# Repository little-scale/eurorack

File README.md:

# Eurorack

Eurorack projects

http://little-scale.com/

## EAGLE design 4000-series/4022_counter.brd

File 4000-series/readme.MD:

# 4000 Series Modules

Simple, cheap CMOS Logic-based Eurorack modules. 

* 4022 Eight Stage Counter
* 4024 Seven Stage Binary Counter Module 
* 4028 Binary Addressable Sequencer Module
* 4093 Quad LFO

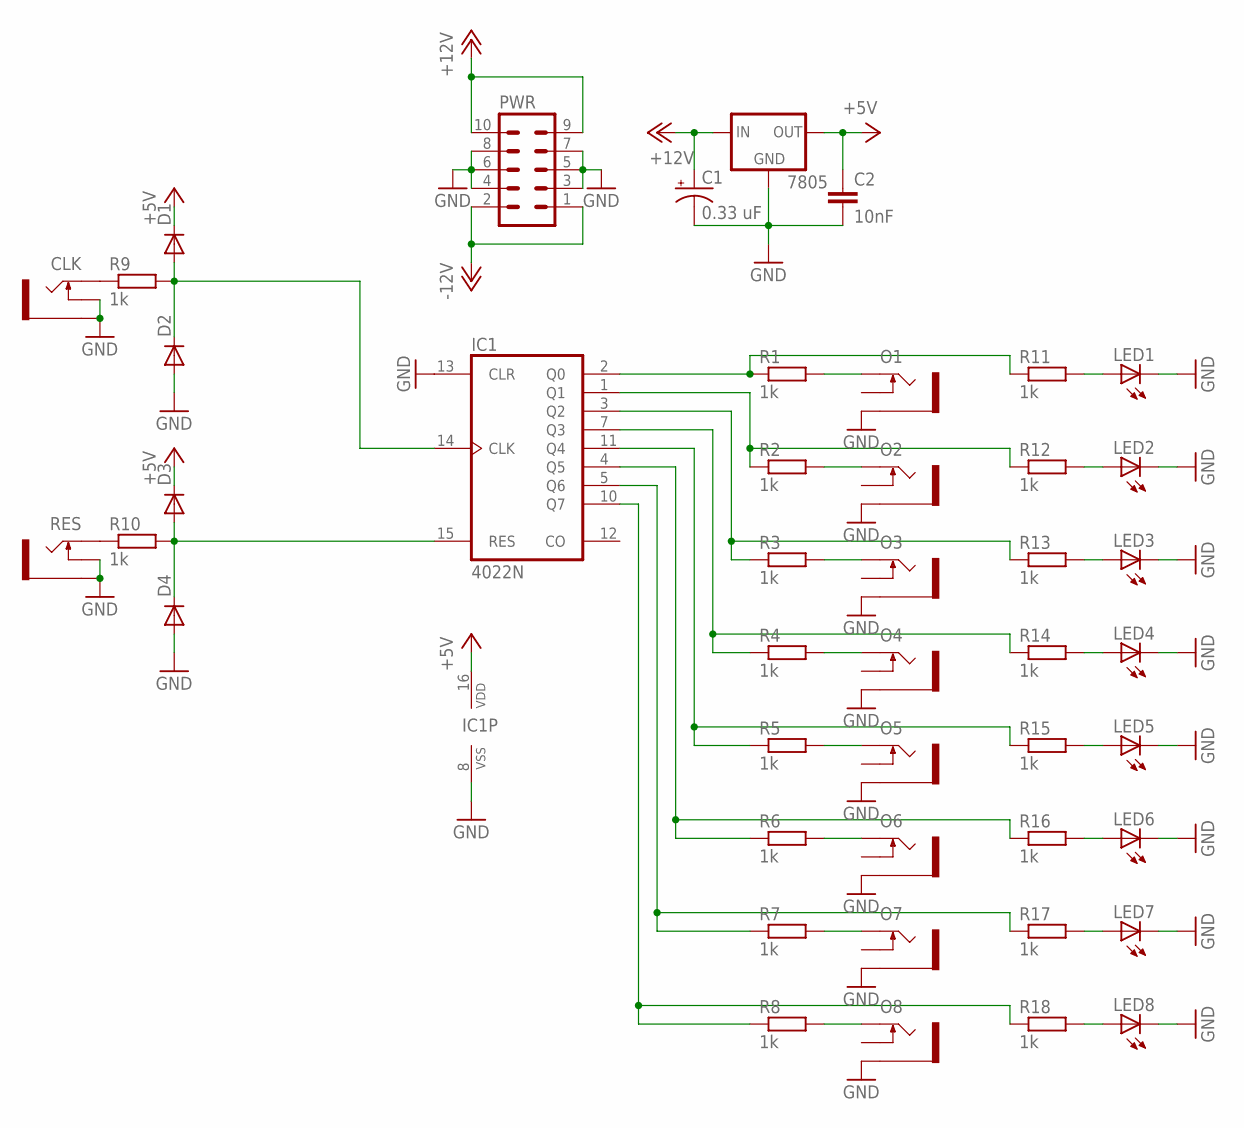
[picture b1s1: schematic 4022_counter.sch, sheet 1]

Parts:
7805: 78XXS
C1: 0.33 uF; E2,5-7
C2: 10nF; CAP-PTH-10MM
CLK: THONKICONNNEW; WQP-PJ301M-12_JACK
D1, D2, D3, D4: SMALL_DIODEDO35-7; DO35-7
IC1: 4022N; DIL16
LED1, LED2, LED3, LED4, LED5, LED6, LED7, LED8: LED3MM
O1, O2, O3, O4, O5, O6, O7, O8: THONKICONNNEW; WQP-PJ301M-12_JACK
PWR: EURO_POWER_HEADERFAT_PADS; EURO_PWR_HEADER_FAT
R1, R2, R3, R4, R5, R6, R7, R8, R9, R10, R11, R12, R13, R14, R15, R16, R17, R18: 1k; 7MM_RESISTOR
RES: THONKICONNNEW; WQP-PJ301M-12_JACK

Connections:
+5V: 7805.OUT, C2.1, D1.C, D3.C, IC1.16 (VDD)
+12V: 7805.IN, C1.+, PWR.9, PWR.10
-12V: PWR.1, PWR.2
GND: 7805.GND, C1.-, C2.2, CLK.P$2_SWITCH (SWITCH), CLK.P$3_SLEEVE (SLEEVE), D2.A, D4.A, IC1.8 (VSS), IC1.13 (CLR), LED1.K (C), LED2.K (C), LED3.K (C), LED4.K (C), LED5.K (C), LED6.K (C), LED7.K (C), LED8.K (C), O1.P$3_SLEEVE (SLEEVE), O2.P$3_SLEEVE (SLEEVE), O3.P$3_SLEEVE (SLEEVE), O4.P$3_SLEEVE (SLEEVE), O5.P$3_SLEEVE (SLEEVE), O6.P$3_SLEEVE (SLEEVE), O7.P$3_SLEEVE (SLEEVE), O8.P$3_SLEEVE (SLEEVE), PWR.3, PWR.4, PWR.5, PWR.6, PWR.7, PWR.8, RES.P$2_SWITCH (SWITCH), RES.P$3_SLEEVE (SLEEVE)
unnamed: CLK.P$1_TIP (TIP), R9.1
unnamed: R10.1, RES.P$1_TIP (TIP)
unnamed: IC1.1 (Q1), R2.1, R12.1
unnamed: IC1.3 (Q2), R3.1, R13.1
unnamed: IC1.7 (Q3), R4.1, R14.1
unnamed: IC1.11 (Q4), R5.1, R15.1
unnamed: O1.P$1_TIP (TIP), R1.2
unnamed: O2.P$1_TIP (TIP), R2.2
unnamed: O3.P$1_TIP (TIP), R3.2
unnamed: D1.A, D2.C, IC1.14 (CLK), R9.2
unnamed: IC1.2 (Q0), R1.1, R11.1
unnamed: D3.A, D4.C, IC1.15 (RES), R10.2
unnamed: LED1.A, R11.2
unnamed: O4.P$1_TIP (TIP), R4.2
unnamed: LED2.A, R12.2
unnamed: O5.P$1_TIP (TIP), R5.2
unnamed: LED3.A, R13.2
unnamed: O6.P$1_TIP (TIP), R6.2
unnamed: LED4.A, R14.2
unnamed: O7.P$1_TIP (TIP), R7.2
unnamed: LED5.A, R15.2
unnamed: IC1.4 (Q5), R6.1, R16.1
unnamed: LED6.A, R16.2
unnamed: IC1.5 (Q6), R7.1, R17.1
unnamed: LED7.A, R17.2
unnamed: IC1.10 (Q7), R8.1, R18.1
unnamed: LED8.A, R18.2
unnamed: O8.P$1_TIP (TIP), R8.2

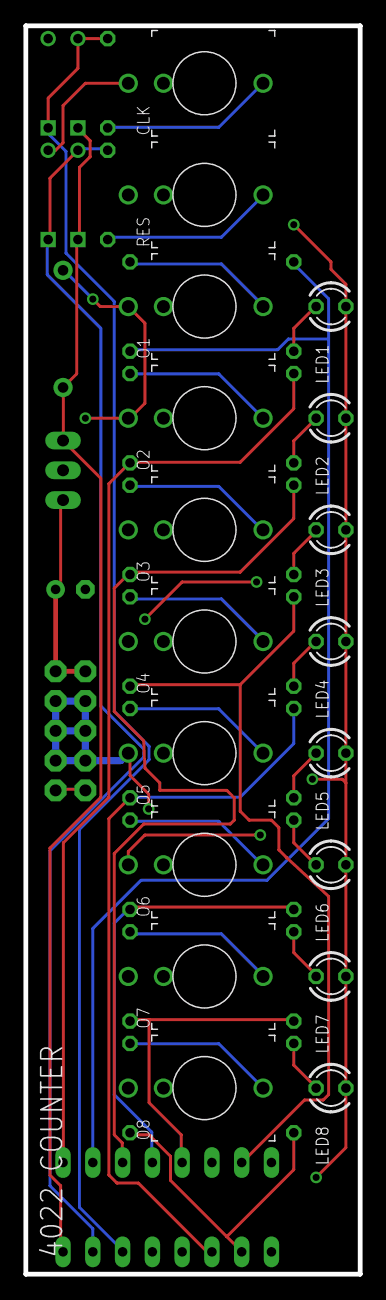
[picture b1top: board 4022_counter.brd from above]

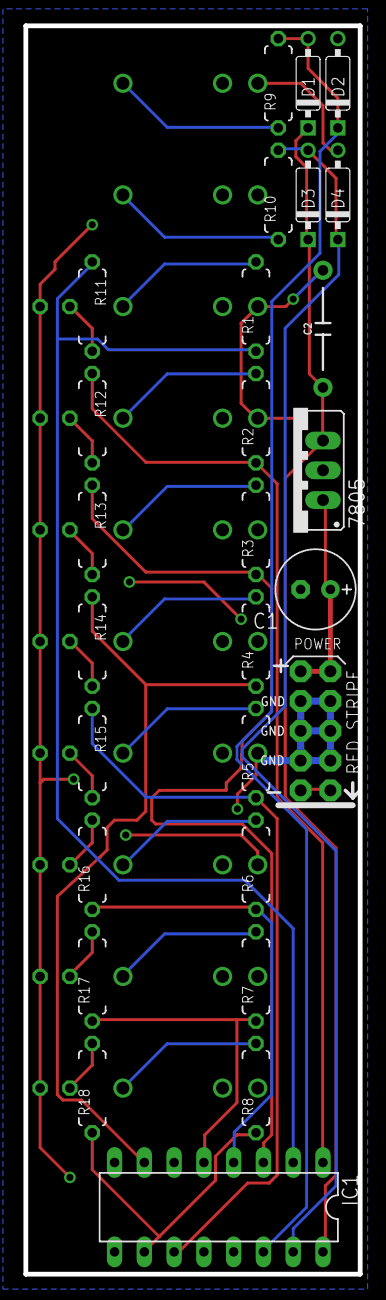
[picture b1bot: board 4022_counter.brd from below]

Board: 2 copper layers, 28.5 x 106.5 mm, 45 parts (27 on the bottom side), 32 nets.

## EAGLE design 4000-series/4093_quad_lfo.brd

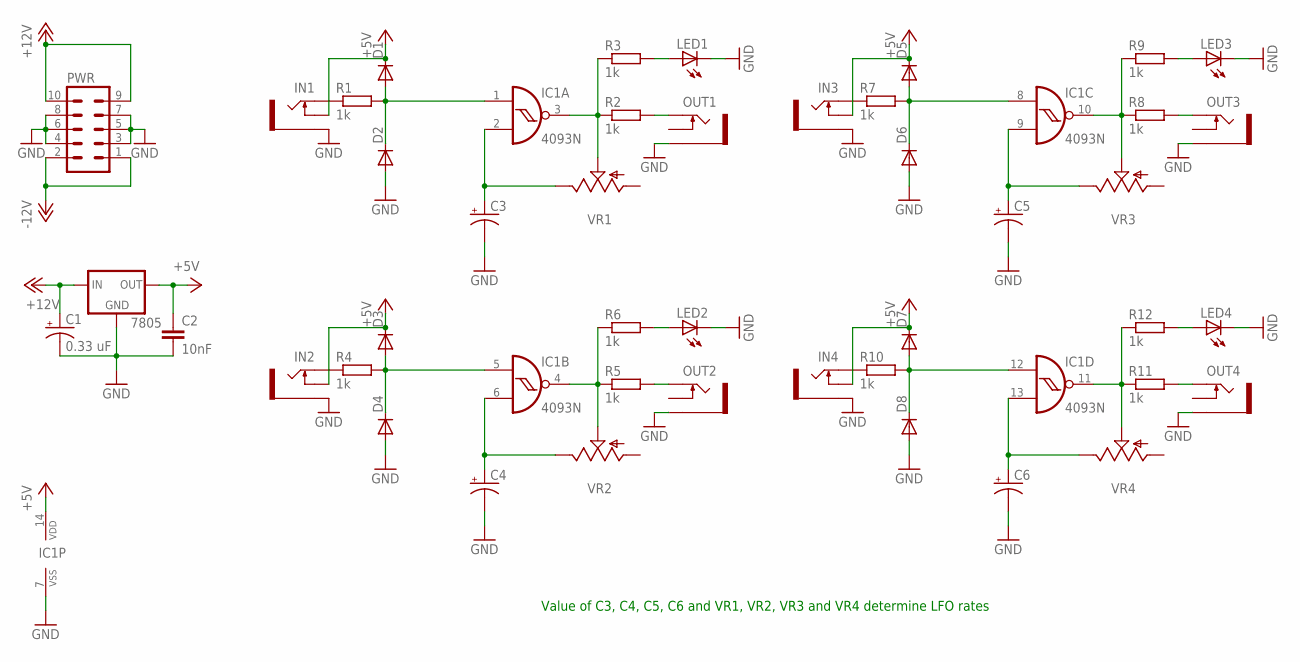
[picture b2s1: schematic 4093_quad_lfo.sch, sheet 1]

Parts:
7805: 78XXS
C1: 0.33 uF; E2,5-7
C2: 10nF; CAP-PTH-10MM
C3, C4, C5, C6: CPOL-USE2.5-7; E2,5-7
D1, D2, D3, D4, D5, D6, D7, D8: SMALL_DIODEDO35-7; DO35-7
IC1: 4093N; DIL14
IN1, IN2, IN3, IN4: THONKICONNNEW; WQP-PJ301M-12_JACK
LED1, LED2, LED3, LED4: LED3MM
OUT1, OUT2, OUT3, OUT4: THONKICONNNEW; WQP-PJ301M-12_JACK
PWR: EURO_POWER_HEADERFAT_PADS; EURO_PWR_HEADER_FAT
R1, R2, R3, R4, R5, R6, R7, R8, R9, R10, R11, R12: 1k; 7MM_RESISTOR
VR1, VR2, VR3, VR4: 9MM_SNAP-IN_POT_; 9MM_SNAP-IN_POT

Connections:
+5V: 7805.OUT, C2.1, D1.C, D3.C, D5.C, D7.C, IC1.14 (VDD), IN1.P$2_SWITCH (SWITCH), IN2.P$2_SWITCH (SWITCH), IN3.P$2_SWITCH (SWITCH), IN4.P$2_SWITCH (SWITCH)
+12V: 7805.IN, C1.+, PWR.9, PWR.10
-12V: PWR.1, PWR.2
GND: 7805.GND, C1.-, C2.2, C3.-, C4.-, C5.-, C6.-, D2.A, D4.A, D6.A, D8.A, IC1.7 (VSS), IN1.P$3_SLEEVE (SLEEVE), IN2.P$3_SLEEVE (SLEEVE), IN3.P$3_SLEEVE (SLEEVE), IN4.P$3_SLEEVE (SLEEVE), LED1.K (C), LED2.K (C), LED3.K (C), LED4.K (C), OUT1.P$3_SLEEVE (SLEEVE), OUT2.P$3_SLEEVE (SLEEVE), OUT3.P$3_SLEEVE (SLEEVE), OUT4.P$3_SLEEVE (SLEEVE), PWR.3, PWR.4, PWR.5, PWR.6, PWR.7, PWR.8
unnamed: IN1.P$1_TIP (TIP), R1.1
unnamed: D3.A, D4.C, IC1.5 (I0), R4.2
unnamed: LED1.A, R3.2
unnamed: C3.+, IC1.2 (I1), VR1.3 (E)
unnamed: IC1.3 (O), R2.1, R3.1, VR1.2 (S)
unnamed: OUT1.P$1_TIP (TIP), R2.2
unnamed: IN2.P$1_TIP (TIP), R4.1
unnamed: C4.+, IC1.6 (I1), VR2.3 (E)
unnamed: IC1.4 (O), R5.1, R6.1, VR2.2 (S)
unnamed: OUT2.P$1_TIP (TIP), R5.2
unnamed: LED2.A, R6.2
unnamed: D5.A, D6.C, IC1.8 (I0), R7.2
unnamed: IN3.P$1_TIP (TIP), R7.1
unnamed: C5.+, IC1.9 (I1), VR3.3 (E)
unnamed: IC1.10 (O), R8.1, R9.1, VR3.2 (S)
unnamed: OUT3.P$1_TIP (TIP), R8.2
unnamed: LED3.A, R9.2
unnamed: D1.A, D2.C, IC1.1 (I0), R1.2
unnamed: D7.A, D8.C, IC1.12 (I0), R10.2
unnamed: IN4.P$1_TIP (TIP), R10.1
unnamed: C6.+, IC1.13 (I1), VR4.3 (E)
unnamed: IC1.11 (O), R11.1, R12.1, VR4.2 (S)
unnamed: OUT4.P$1_TIP (TIP), R11.2
unnamed: LED4.A, R12.2

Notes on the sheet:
Value of C3, C4, C5, C6 and VR1, VR2, VR3 and VR4 determine LFO rates

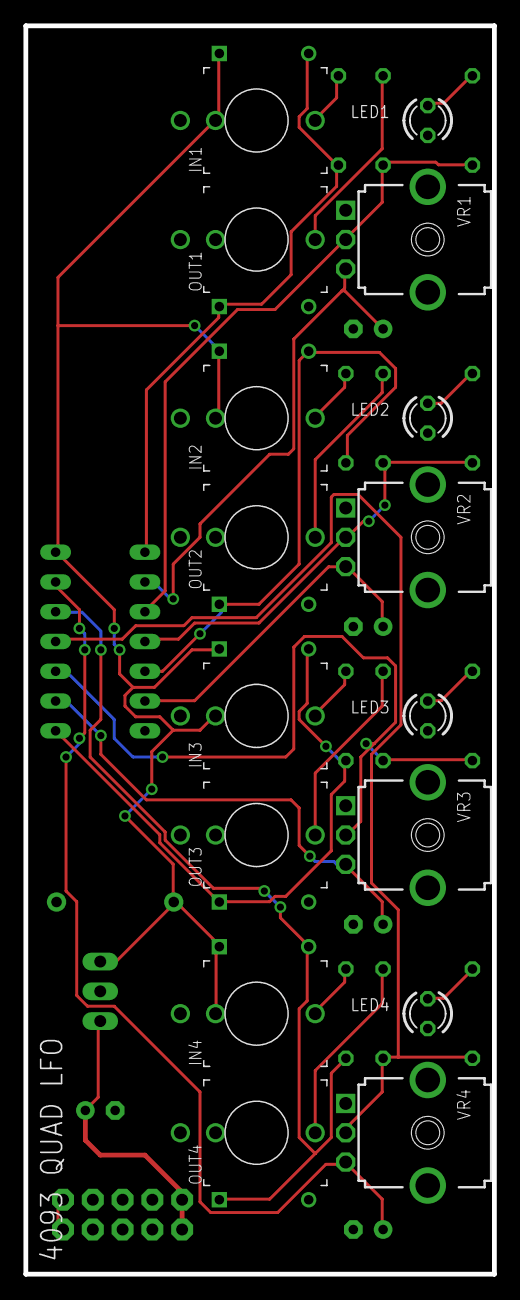
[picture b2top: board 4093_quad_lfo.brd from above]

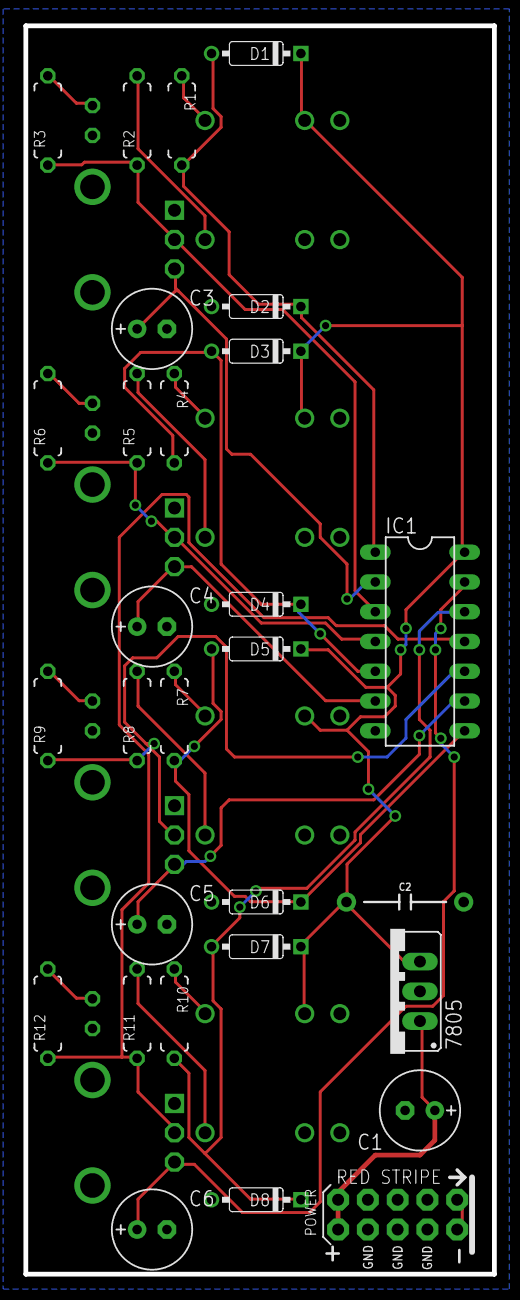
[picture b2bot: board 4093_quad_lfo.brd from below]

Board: 2 copper layers, 40.0 x 106.5 mm, 45 parts (29 on the bottom side), 28 nets.

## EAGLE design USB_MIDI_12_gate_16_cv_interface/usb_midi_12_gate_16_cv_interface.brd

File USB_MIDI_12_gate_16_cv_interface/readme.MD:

This is a USB-powered, Teensy-based interface that has 16 CV outputs and 12 gate outputs. 
USB MIDI channels 1 - 8 are mapped to CV outputs 1 - 16 for pitch and velocity, and gates 1 - 8 for note on and off events. 
Gates 9 - 12 are mapped to note on and off events only on channel 9, 
and also will send a sync and transport signal based on MIDI clock messages if received. 
CV is 12 bit from 0V to 4V, gates 1 - 8 are 0 and 5V, and gates 9 - 12 are 0 and 3.3v.

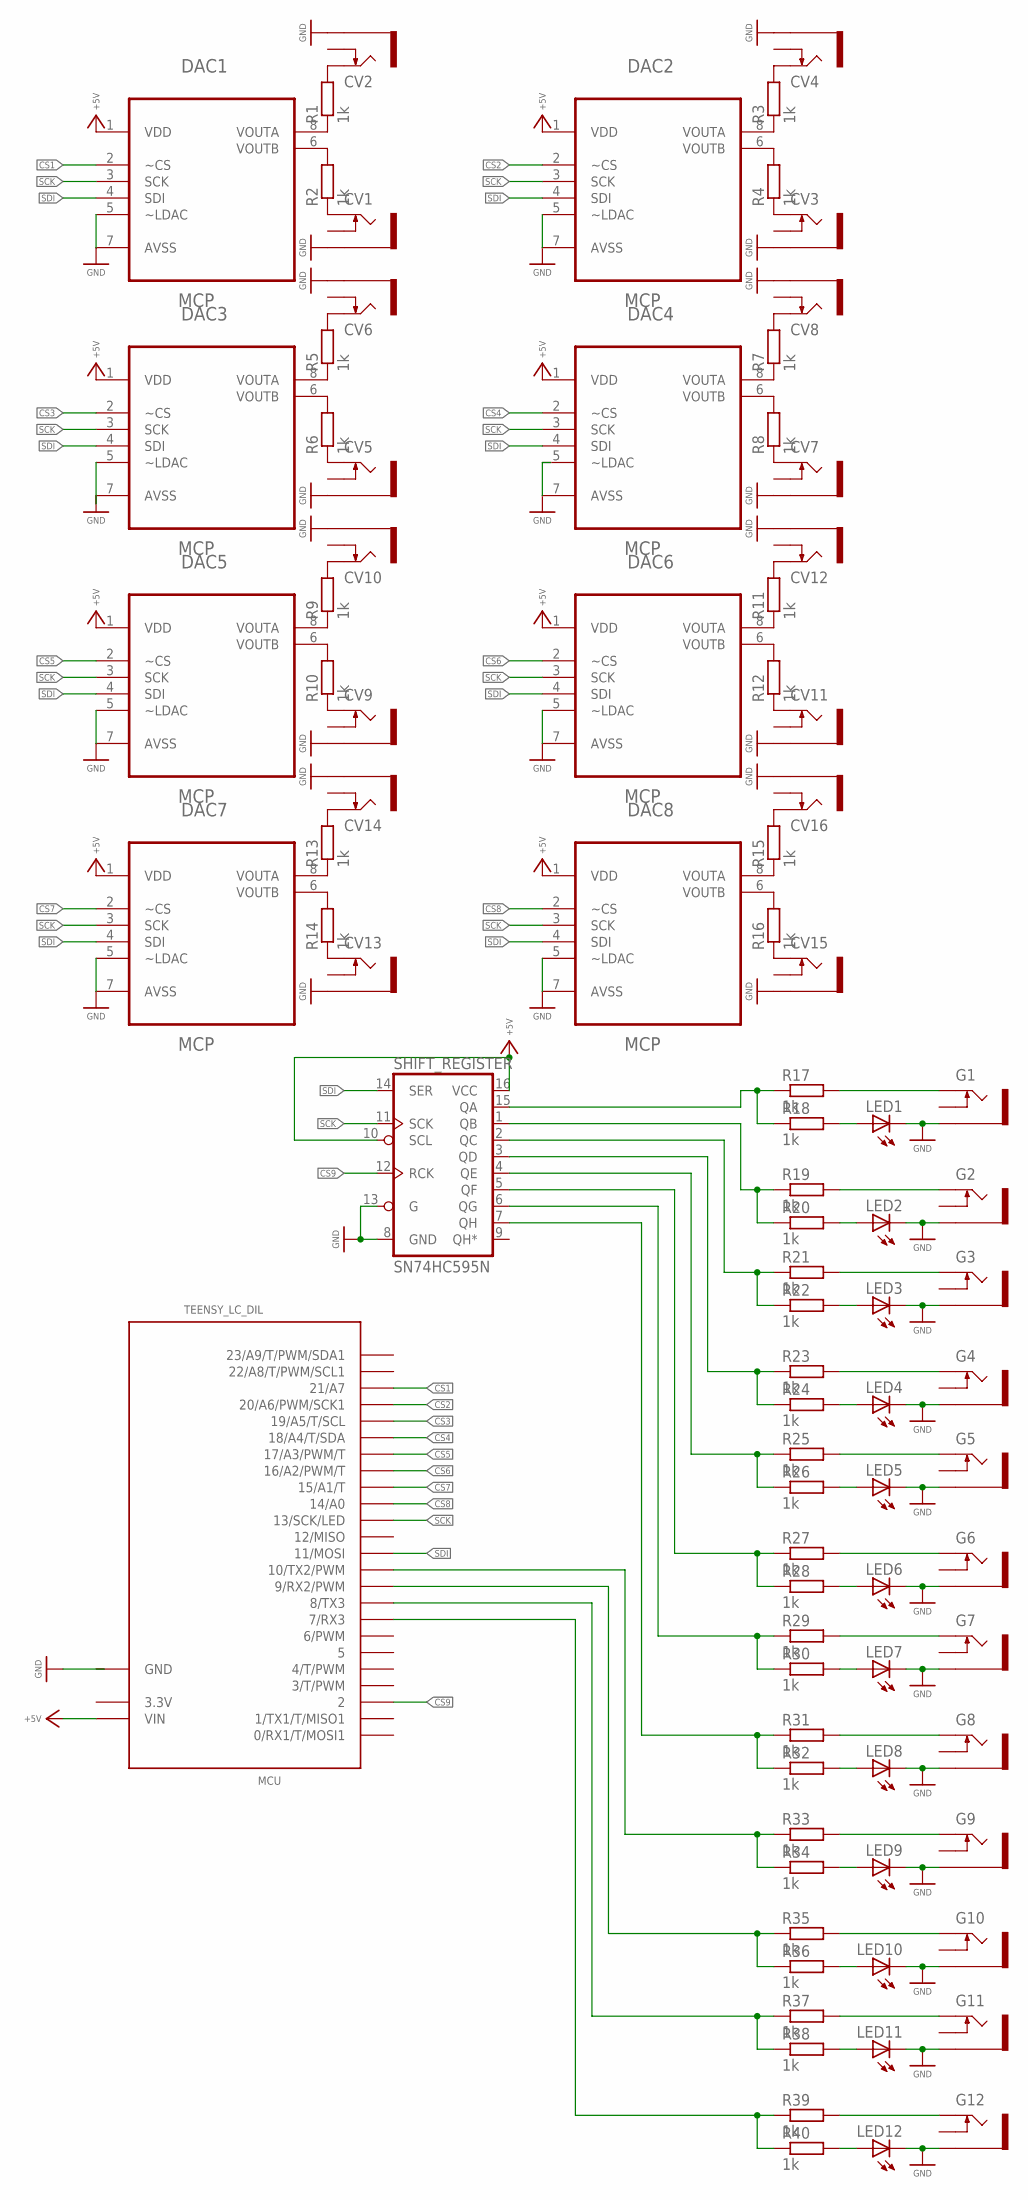
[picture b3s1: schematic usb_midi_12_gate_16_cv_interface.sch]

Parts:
CV1, CV2, CV3, CV4, CV5, CV6, CV7, CV8, CV9, CV10, CV11, CV12, CV13, CV14, CV15, CV16: THONKICONNNEW; WQP-PJ301M-12_JACK
DAC1, DAC2, DAC3, DAC4, DAC5, DAC6, DAC7, DAC8: MCP; DIP254P762X432-8
G1, G2, G3, G4, G5, G6, G7, G8, G9, G10, G11, G12: THONKICONNNEW; WQP-PJ301M-12_JACK
LED1, LED2, LED3, LED4, LED5, LED6, LED7, LED8, LED9, LED10, LED11, LED12: LED3MM
MCU: TEENSY_LC_DIL; TEENSY_3.0-3.2&LC_DIL
R1, R2, R3, R4, R5, R6, R7, R8, R9, R10, R11, R12, R13, R14, R15, R16, R17, R18, R19, R20, R21, R22, R23, R24, R25, R26, R27, R28, R29, R30, R31, R32, R33, R34, R35, R36, R37, R38, R39, R40: 1k; 10MM_RESISTOR
SHIFT_REGISTER: SN74HC595N; DIP16

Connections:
3.3V: MCU.3.3V
+5V: DAC1.1 (VDD), DAC2.1 (VDD), DAC3.1 (VDD), DAC4.1 (VDD), DAC5.1 (VDD), DAC6.1 (VDD), DAC7.1 (VDD), DAC8.1 (VDD), MCU.VIN, SHIFT_REGISTER.10 (SCL), SHIFT_REGISTER.16 (VCC)
CS1: DAC1.2 (~CS), MCU.21/A7
CS2: DAC2.2 (~CS), MCU.20/A6 (20/A6/PWM/SCK1)
CS3: DAC3.2 (~CS), MCU.19/A5 (19/A5/T/SCL)
CS4: DAC4.2 (~CS), MCU.18/A4 (18/A4/T/SDA)
CS5: DAC5.2 (~CS), MCU.17/A3 (17/A3/PWM/T)
CS6: DAC6.2 (~CS), MCU.16/A2 (16/A2/PWM/T)
CS7: DAC7.2 (~CS), MCU.15/A1 (15/A1/T)
CS8: DAC8.2 (~CS), MCU.14/A0
CS9: MCU.2, SHIFT_REGISTER.12 (RCK)
GND: CV1.P$3_SLEEVE (SLEEVE), CV2.P$3_SLEEVE (SLEEVE), CV3.P$3_SLEEVE (SLEEVE), CV4.P$3_SLEEVE (SLEEVE), CV5.P$3_SLEEVE (SLEEVE), CV6.P$3_SLEEVE (SLEEVE), CV7.P$3_SLEEVE (SLEEVE), CV8.P$3_SLEEVE (SLEEVE), CV9.P$3_SLEEVE (SLEEVE), CV10.P$3_SLEEVE (SLEEVE), CV11.P$3_SLEEVE (SLEEVE), CV12.P$3_SLEEVE (SLEEVE), CV13.P$3_SLEEVE (SLEEVE), CV14.P$3_SLEEVE (SLEEVE), CV15.P$3_SLEEVE (SLEEVE), CV16.P$3_SLEEVE (SLEEVE), DAC1.5 (~LDAC), DAC1.7 (AVSS), DAC2.5 (~LDAC), DAC2.7 (AVSS), DAC3.7 (AVSS), DAC4.7 (AVSS), DAC5.5 (~LDAC), DAC5.7 (AVSS), DAC6.5 (~LDAC), DAC6.7 (AVSS), DAC7.5 (~LDAC), DAC7.7 (AVSS), DAC8.5 (~LDAC), DAC8.7 (AVSS), G1.P$3_SLEEVE (SLEEVE), G2.P$3_SLEEVE (SLEEVE), G3.P$3_SLEEVE (SLEEVE), G4.P$3_SLEEVE (SLEEVE), G5.P$3_SLEEVE (SLEEVE), G6.P$3_SLEEVE (SLEEVE), G7.P$3_SLEEVE (SLEEVE), G8.P$3_SLEEVE (SLEEVE), G9.P$3_SLEEVE (SLEEVE), G10.P$3_SLEEVE (SLEEVE), G11.P$3_SLEEVE (SLEEVE), G12.P$3_SLEEVE (SLEEVE), LED1.K (C), LED2.K (C), LED3.K (C), LED4.K (C), LED5.K (C), LED6.K (C), LED7.K (C), LED8.K (C), LED9.K (C), LED10.K (C), LED11.K (C), LED12.K (C), MCU.AGND (GND), MCU.GND, SHIFT_REGISTER.8 (GND), SHIFT_REGISTER.13 (G)
unnamed: DAC1.6 (VOUTB), R2.2
unnamed: DAC1.8 (VOUTA), R1.1
unnamed: DAC2.8 (VOUTA), R3.1
unnamed: DAC2.6 (VOUTB), R4.2
unnamed: DAC3.8 (VOUTA), R5.1
unnamed: DAC3.6 (VOUTB), R6.2
unnamed: DAC4.8 (VOUTA), R7.1
unnamed: DAC4.6 (VOUTB), R8.2
unnamed: DAC5.8 (VOUTA), R9.1
unnamed: DAC5.6 (VOUTB), R10.2
unnamed: DAC6.8 (VOUTA), R11.1
unnamed: DAC6.6 (VOUTB), R12.2
unnamed: DAC7.8 (VOUTA), R13.1
unnamed: DAC7.6 (VOUTB), R14.2
unnamed: DAC8.8 (VOUTA), R15.1
unnamed: DAC8.6 (VOUTB), R16.2
unnamed: CV1.P$1_TIP (TIP), R2.1
unnamed: CV2.P$1_TIP (TIP), R1.2
unnamed: CV4.P$1_TIP (TIP), R3.2
unnamed: CV3.P$1_TIP (TIP), R4.1
unnamed: CV5.P$1_TIP (TIP), R6.1
unnamed: CV6.P$1_TIP (TIP), R5.2
unnamed: CV7.P$1_TIP (TIP), R8.1
unnamed: CV8.P$1_TIP (TIP), R7.2
unnamed: CV9.P$1_TIP (TIP), R10.1
unnamed: CV10.P$1_TIP (TIP), R9.2
unnamed: CV11.P$1_TIP (TIP), R12.1
unnamed: CV12.P$1_TIP (TIP), R11.2
unnamed: CV13.P$1_TIP (TIP), R14.1
unnamed: CV14.P$1_TIP (TIP), R13.2
unnamed: CV15.P$1_TIP (TIP), R16.1
unnamed: CV16.P$1_TIP (TIP), R15.2
unnamed: G9.P$1_TIP (TIP), R33.2
unnamed: LED9.A, R34.2
unnamed: MCU.10 (10/TX2/PWM), R33.1, R34.1
unnamed: G10.P$1_TIP (TIP), R35.2
unnamed: LED10.A, R36.2
unnamed: MCU.9 (9/RX2/PWM), R35.1, R36.1
unnamed: G11.P$1_TIP (TIP), R37.2
unnamed: LED11.A, R38.2
unnamed: MCU.8 (8/TX3), R37.1, R38.1
unnamed: G12.P$1_TIP (TIP), R39.2
unnamed: LED12.A, R40.2
unnamed: MCU.7 (7/RX3), R39.1, R40.1
unnamed: G1.P$1_TIP (TIP), R17.2
unnamed: R17.1, R18.1, SHIFT_REGISTER.15 (QA)
unnamed: LED1.A, R18.2
unnamed: G2.P$1_TIP (TIP), R19.2
unnamed: LED2.A, R20.2
unnamed: R19.1, R20.1, SHIFT_REGISTER.1 (QB)
unnamed: G3.P$1_TIP (TIP), R21.2
unnamed: LED3.A, R22.2
unnamed: R21.1, R22.1, SHIFT_REGISTER.2 (QC)
unnamed: G4.P$1_TIP (TIP), R23.2
unnamed: LED4.A, R24.2
unnamed: R23.1, R24.1, SHIFT_REGISTER.3 (QD)
unnamed: G5.P$1_TIP (TIP), R25.2
unnamed: LED5.A, R26.2
unnamed: R25.1, R26.1, SHIFT_REGISTER.4 (QE)
unnamed: G6.P$1_TIP (TIP), R27.2
unnamed: LED6.A, R28.2
unnamed: R27.1, R28.1, SHIFT_REGISTER.5 (QF)
unnamed: G7.P$1_TIP (TIP), R29.2
unnamed: LED7.A, R30.2
unnamed: R29.1, R30.1, SHIFT_REGISTER.6 (QG)
unnamed: G8.P$1_TIP (TIP), R31.2
unnamed: LED8.A, R32.2
unnamed: R31.1, R32.1, SHIFT_REGISTER.7 (QH)
SCK: DAC1.3 (SCK), DAC2.3 (SCK), DAC3.3 (SCK), DAC4.3 (SCK), DAC5.3 (SCK), DAC6.3 (SCK), DAC7.3 (SCK), DAC8.3 (SCK), MCU.13 (13/SCK/LED), SHIFT_REGISTER.11 (SCK)
SDI: DAC1.4 (SDI), DAC2.4 (SDI), DAC3.4 (SDI), DAC4.4 (SDI), DAC5.4 (SDI), DAC6.4 (SDI), DAC7.4 (SDI), DAC8.4 (SDI), MCU.11 (11/MOSI), SHIFT_REGISTER.14 (SER)

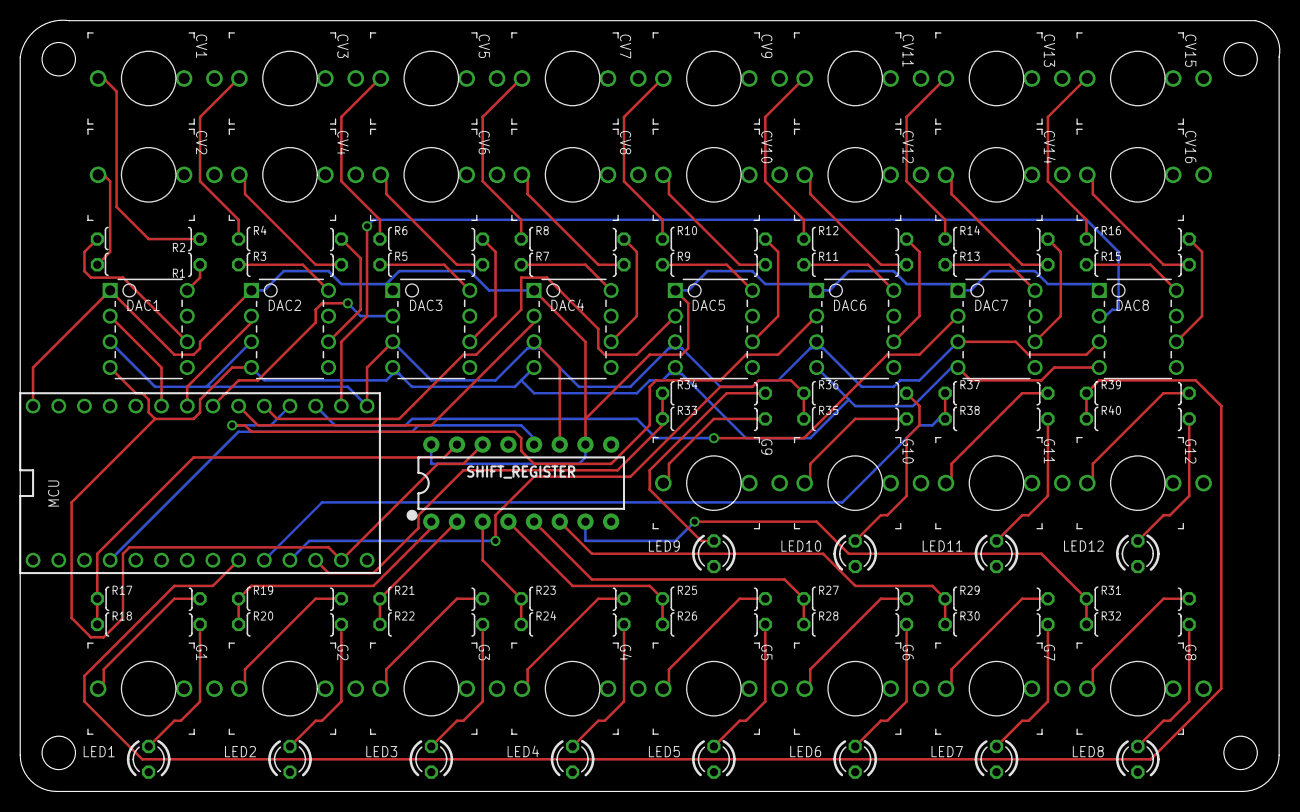
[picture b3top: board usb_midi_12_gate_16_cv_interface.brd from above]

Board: 2 copper layers, 124.5 x 76.2 mm, 90 parts (0 on the bottom side), 81 nets.

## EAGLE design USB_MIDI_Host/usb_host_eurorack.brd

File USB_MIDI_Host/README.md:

Examples of using Teensy 3.6 as a mediator between USB MIDI and Eurorack

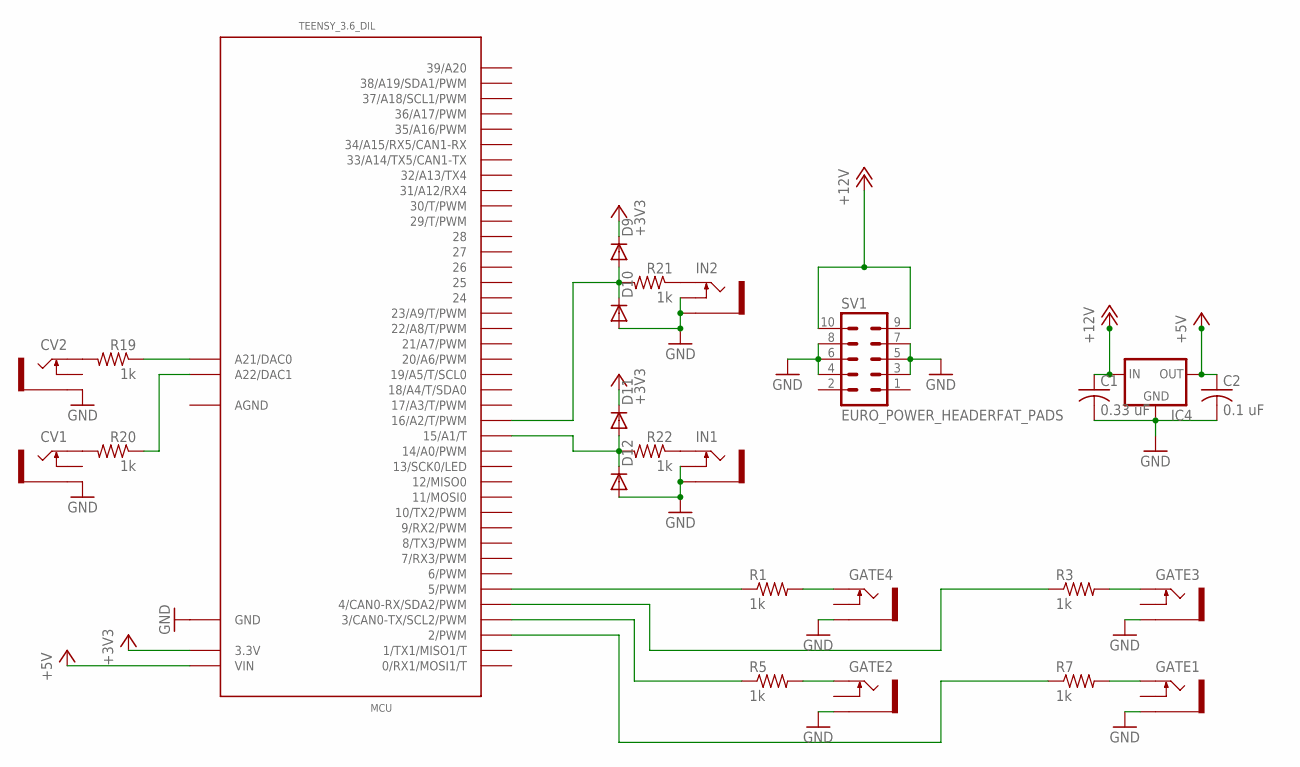
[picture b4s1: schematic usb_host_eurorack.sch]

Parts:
C1: 0.33 uF; C025-030X050
C2: 0.1 uF; C025-030X050
CV1, CV2: PJ302M
D9, D10, D11, D12: SMALL_DIODEDO35-7; DO35-7
GATE1, GATE2, GATE3, GATE4: PJ302M
IC4: 78XXL
IN1, IN2: PJ302M
MCU: TEENSY_3.6_DIL
R1, R3, R5, R7, R19, R20, R21, R22: 1k; 0207/10
SV1: EURO_POWER_HEADERFAT_PADS; EURO_PWR_HEADER_FAT

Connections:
+3V3: D9.C, D11.C, MCU.3.3V, MCU.3.3V3 (3.3V)
+5V: C2.1, IC4.OUT, MCU.VIN
+12V: C1.1, IC4.IN, SV1.9, SV1.10
AGND: MCU.AGND
GND: C1.2, C2.2, CV1.GND (SLEEVE), CV2.GND (SLEEVE), D10.A, D12.A, GATE1.GND (SLEEVE), GATE2.GND (SLEEVE), GATE3.GND (SLEEVE), GATE4.GND (SLEEVE), IC4.GND, IN1.GND (SLEEVE), IN1.SW (SWITCH), IN2.GND (SLEEVE), IN2.SW (SWITCH), MCU.GND, MCU.GND1 (GND), SV1.3, SV1.4, SV1.5, SV1.6, SV1.7, SV1.8
I1: D9.A, D10.C, MCU.16/A2 (16/A2/T/PWM), R21.2
I2: D11.A, D12.C, MCU.15/A1 (15/A1/T), R22.2
unnamed: GATE4.TIP, R1.2
unnamed: MCU.A22 (A22/DAC1), R20.1
unnamed: MCU.5 (5/PWM), R1.1
unnamed: GATE3.TIP, R3.2
unnamed: MCU.A21 (A21/DAC0), R19.1
unnamed: MCU.4 (4/CAN0-RX/SDA2/PWM), R3.1
unnamed: GATE2.TIP, R5.2
unnamed: MCU.3 (3/CAN0-TX/SCL2/PWM), R5.1
unnamed: GATE1.TIP, R7.2
unnamed: MCU.2 (2/PWM), R7.1
unnamed: IN2.TIP, R21.1
unnamed: IN1.TIP, R22.1
unnamed: CV2.TIP, R19.2
unnamed: CV1.TIP, R20.2

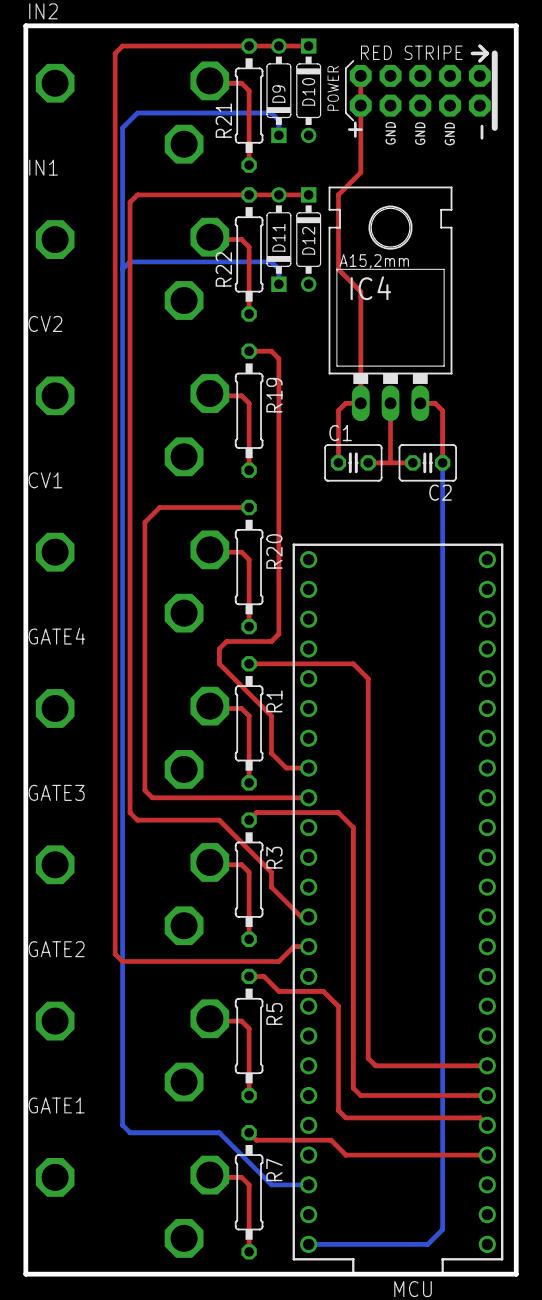
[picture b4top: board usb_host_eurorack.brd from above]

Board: 2 copper layers, 41.8 x 106.5 mm, 25 parts (0 on the bottom side), 20 nets.

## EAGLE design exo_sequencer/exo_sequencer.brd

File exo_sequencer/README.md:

# Exo Sequencer

A sixteen step sequencer with CV and trigger out. 

The step order is selected via a number of ways: 

• A gate signal sent to the INC input will increment the sequencer

• A gate signal sent to the DEC input will increment the sequencer

• An address as a four bit binary value (from 0000 to 1111) sent to A0, A1, A2 and A3 will select that step

• A voltage value sent to the STEP input will select that step

These methods of step selection are not mutually exclusive, and will operate simulatenously. 

The length control sets the length of the pattern. This can be modulated using a control voltage. 
The offset control sets the offset of the pattern. This can be modulated using a control voltage.

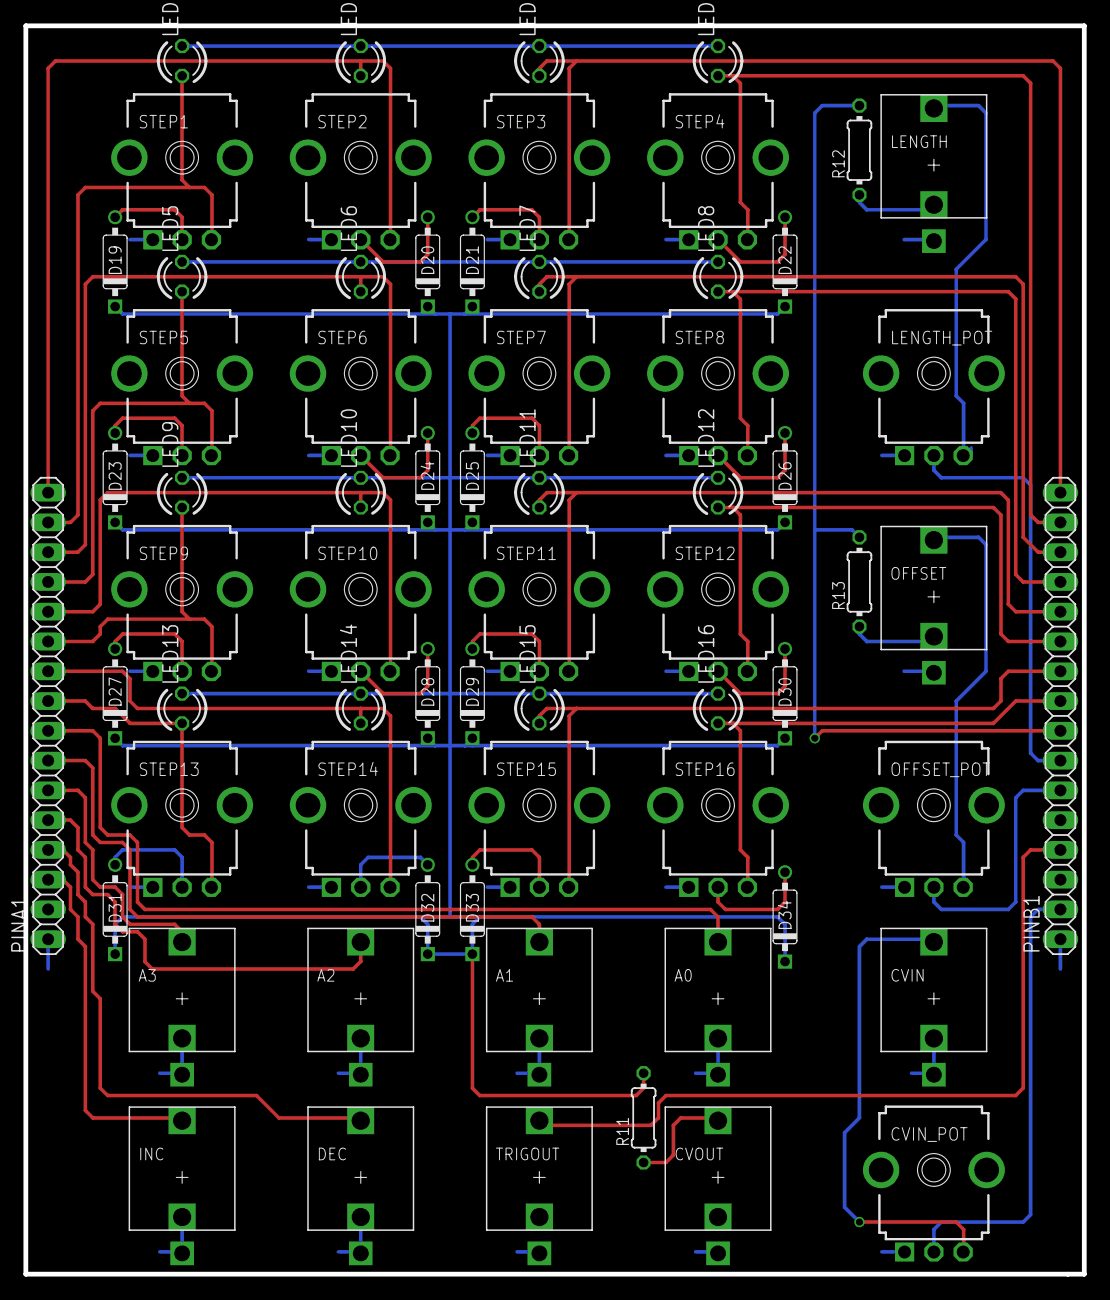
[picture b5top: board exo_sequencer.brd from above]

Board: 2 copper layers, 90.3 x 106.5 mm, 67 parts (0 on the bottom side), 18 nets.

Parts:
A0, A1, A2, A3: THONKICONN
CVIN: THONKICONN
CVIN_POT: 9MM_SNAP-IN_POT
CVOUT: THONKICONN
D19, D20, D21, D22, D23, D24, D25, D26, D27, D28, D29, D30, D31, D32, D33, D34: DO35-7
DEC: THONKICONN
INC: THONKICONN
LED1, LED2, LED3, LED4, LED5, LED6, LED7, LED8, LED9, LED10, LED11, LED12, LED13, LED14, LED15, LED16: LED3MM
LENGTH: THONKICONN
LENGTH_POT: 9MM_SNAP-IN_POT
OFFSET: THONKICONN
OFFSET_POT: 9MM_SNAP-IN_POT
PINA1: 1X16
PINB1: 1X16
R11, R12, R13: 0204/7
STEP1, STEP2, STEP3, STEP4, STEP5, STEP6, STEP7, STEP8, STEP9, STEP10, STEP11, STEP12, STEP13, STEP14, STEP15, STEP16: 9MM_SNAP-IN_POT
TRIGOUT: THONKICONN

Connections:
G: LED1.K, LED4.K, LED5.K, LED8.K, LED9.K, LED12.K, LED13.K, LED16.K, PINA1.1, PINB1.1
S$1: LED2.A, PINA1.16
S$2: LED1.A, PINA1.15
S$5: LED10.A, PINA1.12
S$6: LED16.A, PINB1.9
S$7: LED14.A, PINA1.10
S$8: LED13.A, PINA1.9
S$9: LED9.A, PINA1.11
S$10: LED3.A, PINB1.16
S$11: LED7.A, PINB1.14
S$12: LED4.A, PINB1.15
S$13: LED11.A, PINB1.12
S$14: LED8.A, PINB1.13
S$16: LED12.A, PINB1.11
S$35: D27.C, D28.C, D29.C, D30.C
S$38: D23.C, D24.C, D25.C, D26.C
S$49: PINB1.8, R12.2, R13.2
S$92: D19.C, D20.C, D21.C, D22.C, D31.C, D32.C, D33.C, D34.C, R11.2

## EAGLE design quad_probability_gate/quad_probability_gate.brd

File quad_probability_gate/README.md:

# Quad Probability Gate

A module that has one gate input, one cv input and four gate outputs. 

The cv input sets the likelihood (from 0% / 0v to 100% / 5v) that the input gate is mirrored at each of the four output gates. 

The probability for each output gate is calculated individually. 

Example video: https://www.youtube.com/watch?v=VjSLu_15tZ4

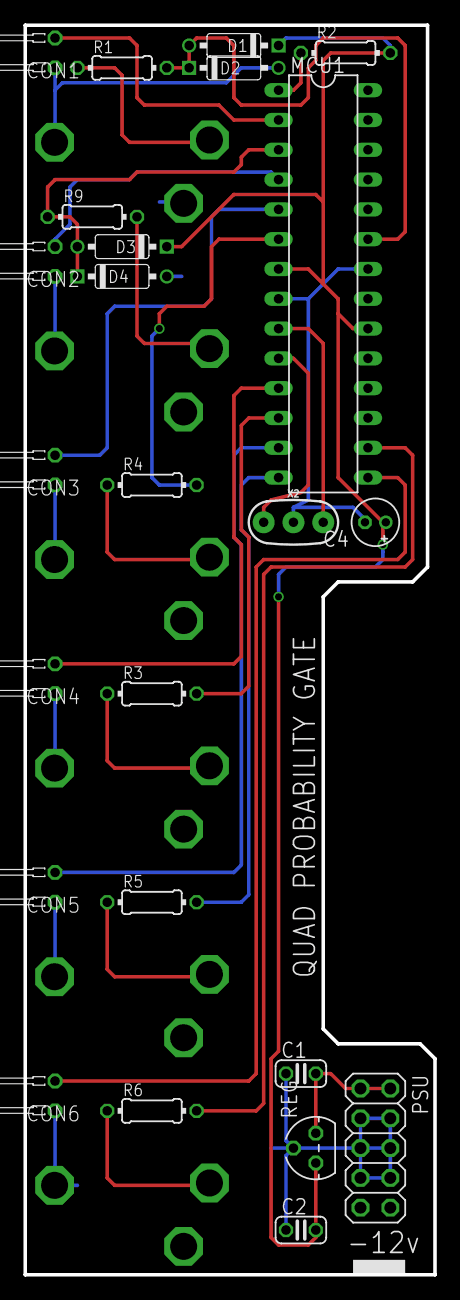
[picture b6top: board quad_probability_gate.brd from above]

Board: 2 copper layers, 34.9 x 106.5 mm, 30 parts (0 on the bottom side), 17 nets.

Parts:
C1, C2: C025-024X044
C4: E1,8-4
CON1, CON2, CON3, CON4, CON5, CON6: PJ302M
D1, D2, D3, D4: DO35-7
LED1, LED2, LED3, LED4, LED5, LED6: LED3MM_H7,5MM
MCU1: DIL28-3
PSU: 2X05
R1, R2, R3, R4, R5, R6, R9: 0204/7
REG: TO92
X2: RESONATOR-PTH-7.6X3.8

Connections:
G: C2.1, D4.A, LED1.A, LED2.A, LED3.A, LED4.A, LED5.A, LED6.A, MCU1.8, MCU1.22, PSU.3, PSU.4, PSU.5, PSU.6, PSU.7, PSU.8, REG.2, X2.2
S$2: LED1.K, MCU1.2
S$3: MCU1.10, X2.1
S$6: D4.C, MCU1.3, R9.1
S$7: MCU1.1, R2.1
S$8: C1.2, PSU.2, REG.3
S$11: D1.A, D2.C, MCU1.23, R1.2
S$14: LED2.K, MCU1.4
S$15: LED3.K, MCU1.5
S$19: MCU1.6, R4.2
S$26: LED4.K, MCU1.11
S$27: MCU1.12, R3.2
S$28: LED5.K, MCU1.13
S$29: MCU1.14, R5.2
S$30: LED6.K, MCU1.15
S$31: MCU1.16, R6.2
VCC: C2.2, D1.C, D3.C, MCU1.7, MCU1.20, R2.2, REG.1

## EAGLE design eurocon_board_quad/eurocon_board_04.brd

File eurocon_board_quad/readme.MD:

Quad Eurorack connector for breadboards

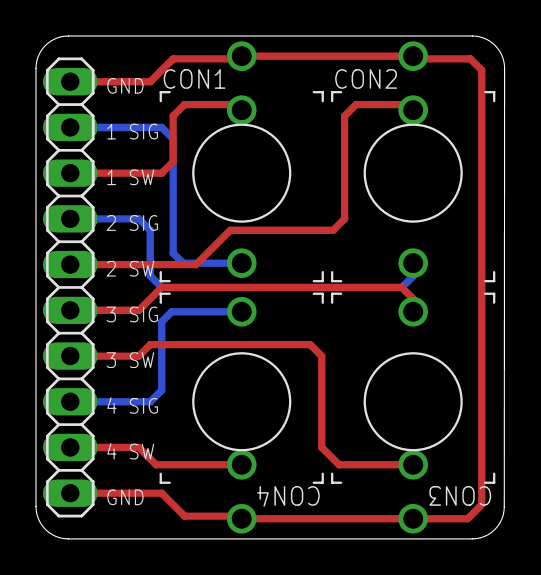
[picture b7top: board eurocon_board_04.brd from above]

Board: 2 copper layers, 26.0 x 27.9 mm, 5 parts (0 on the bottom side), 9 nets.

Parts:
CON1, CON2, CON3, CON4: THONKICONNNEW; WQP-PJ301M-12_JACK
JP1: 1X10

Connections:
GND: CON1.P$3_SLEEVE, CON2.P$3_SLEEVE, CON3.P$3_SLEEVE, CON4.P$3_SLEEVE, JP1.1, JP1.10
unnamed: CON1.P$1_TIP, JP1.2
unnamed: CON1.P$2_SWITCH, JP1.3
unnamed: CON2.P$1_TIP, JP1.4
unnamed: CON2.P$2_SWITCH, JP1.5
unnamed: CON3.P$1_TIP, JP1.6
unnamed: CON3.P$2_SWITCH, JP1.7
unnamed: CON4.P$1_TIP, JP1.8
unnamed: CON4.P$2_SWITCH, JP1.9

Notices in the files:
parts and their libraries:
SparkFun-Capacitors: Licensing: Creative Commons ShareAlike 4.0 International - https://creativecommons.org/licenses/by-sa/4.0
